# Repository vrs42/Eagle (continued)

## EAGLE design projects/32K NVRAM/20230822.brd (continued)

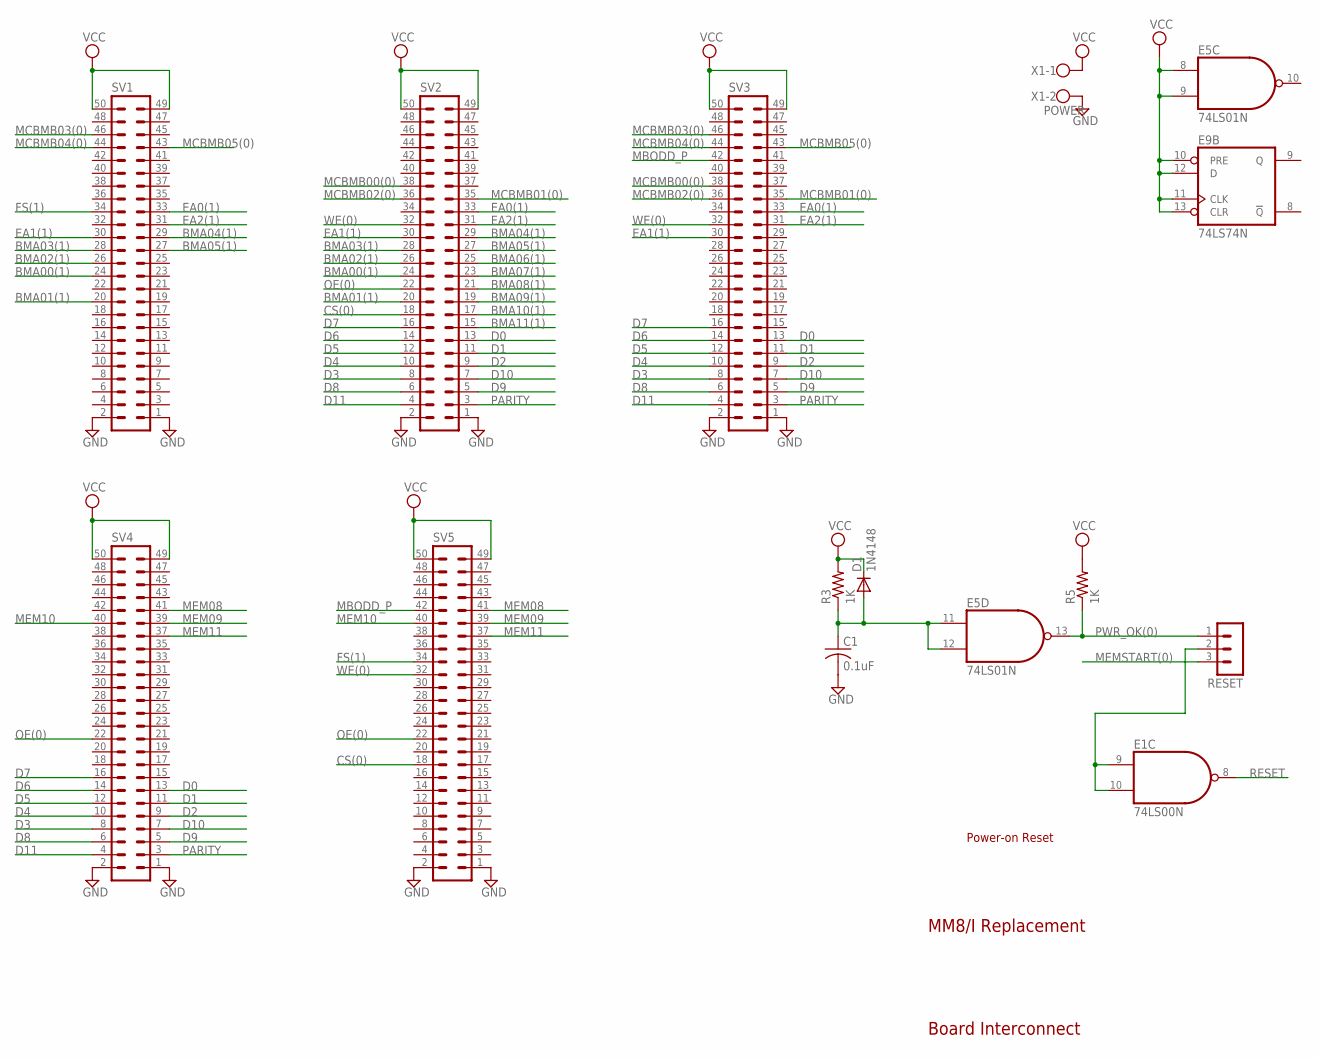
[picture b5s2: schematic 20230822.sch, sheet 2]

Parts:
C1: 0.1uF; C050-025X075
D1: 1N4148; DO35-10
E1: 74LS00N; DIL14
E5: 74LS01N; DIL14
E9: 74LS74N; DIL14
R3, R5: 1K; 0207/10
RESET: MA03-1
SV1, SV2, SV3, SV4, SV5: ML50L
X1: POWER; W237-102

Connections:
BMA00(1): SV1.24, SV2.24; also elsewhere on the board
BMA01(1): SV1.20, SV2.20; also elsewhere on the board
BMA02(1): SV1.26, SV2.26; also elsewhere on the board
BMA03(1): SV1.28, SV2.28; also elsewhere on the board
BMA04(1): SV1.29, SV2.29; also elsewhere on the board
BMA05(1): SV1.27, SV2.27; also elsewhere on the board
BMA06(1): SV2.25; also elsewhere on the board
BMA07(1): SV2.23; also elsewhere on the board
BMA08(1): SV2.21; also elsewhere on the board
BMA09(1): SV2.19; also elsewhere on the board
BMA10(1): SV2.17; also elsewhere on the board
BMA11(1): SV2.15; also elsewhere on the board
CS(0): SV2.18, SV5.18; also elsewhere on the board
D0: SV2.13, SV3.13, SV4.13; also elsewhere on the board
D1: SV2.11, SV3.11, SV4.11; also elsewhere on the board
D2: SV2.9, SV3.9, SV4.9; also elsewhere on the board
D3: SV2.8, SV3.8, SV4.8; also elsewhere on the board
D4: SV2.10, SV3.10, SV4.10; also elsewhere on the board
D5: SV2.12, SV3.12, SV4.12; also elsewhere on the board
D6: SV2.14, SV3.14, SV4.14; also elsewhere on the board
D7: SV2.16, SV3.16, SV4.16; also elsewhere on the board
D8: SV2.6, SV3.6, SV4.6; also elsewhere on the board
D9: SV2.5, SV3.5, SV4.5; also elsewhere on the board
D10: SV2.7, SV3.7, SV4.7; also elsewhere on the board
D11: SV2.4, SV3.4, SV4.4; also elsewhere on the board
EA0(1): SV1.33, SV2.33, SV3.33; also elsewhere on the board
EA1(1): SV1.30, SV2.30, SV3.30; also elsewhere on the board
EA2(1): SV1.31, SV2.31, SV3.31; also elsewhere on the board
FS(1): SV1.34, SV5.34; also elsewhere on the board
GND: C1.2, E1.7 (GND), E5.7 (GND), E9.7 (GND), SV1.1, SV1.2, SV2.1, SV2.2, SV3.1, SV3.2, SV4.1, SV4.2, SV5.1, SV5.2, X1.2; also elsewhere on the board
MBODD_P: SV3.42, SV5.42; also elsewhere on the board
MCBMB00(0): SV2.38, SV3.38; also elsewhere on the board
MCBMB01(0): SV2.35, SV3.35; also elsewhere on the board
MCBMB02(0): SV2.36, SV3.36; also elsewhere on the board
MCBMB03(0): SV1.46, SV3.46; also elsewhere on the board
MCBMB04(0): SV1.44, SV3.44; also elsewhere on the board
MCBMB05(0): SV1.43, SV3.43; also elsewhere on the board
MEM08: SV4.41, SV5.41; also elsewhere on the board
MEM09: SV4.39, SV5.39; also elsewhere on the board
MEM10: SV4.40, SV5.40; also elsewhere on the board
MEM11: SV4.37, SV5.37; also elsewhere on the board
MEMSTART(0): RESET.3; also elsewhere on the board
unnamed: E1.9 (I0), E1.10 (I1), RESET.2
OE(0): SV2.22, SV4.22, SV5.22; also elsewhere on the board
PARITY: SV2.3, SV3.3, SV4.3; also elsewhere on the board
PWR_OK: C1.1, D1.A, E5.11 (I0), E5.12 (I1), R3.1
PWR_OK(0): E5.13 (O), R5.1, RESET.1
RESET: E1.8 (O); also elsewhere on the board
VCC: D1.C, E1.14 (VCC), E5.8 (I0), E5.9 (I1), E5.14 (VCC), E9.10 (PRE), E9.11 (CLK), E9.12 (D), E9.13 (CLR), E9.14 (VCC), R3.2, R5.2, SV1.49, SV1.50, SV2.49, SV2.50, SV3.49, SV3.50, SV4.49, SV4.50, SV5.49, SV5.50, X1.1; also elsewhere on the board
WE(0): SV2.32, SV3.32, SV5.32; also elsewhere on the board

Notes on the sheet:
Board Interconnect
MM8/I Replacement
Power-on Reset

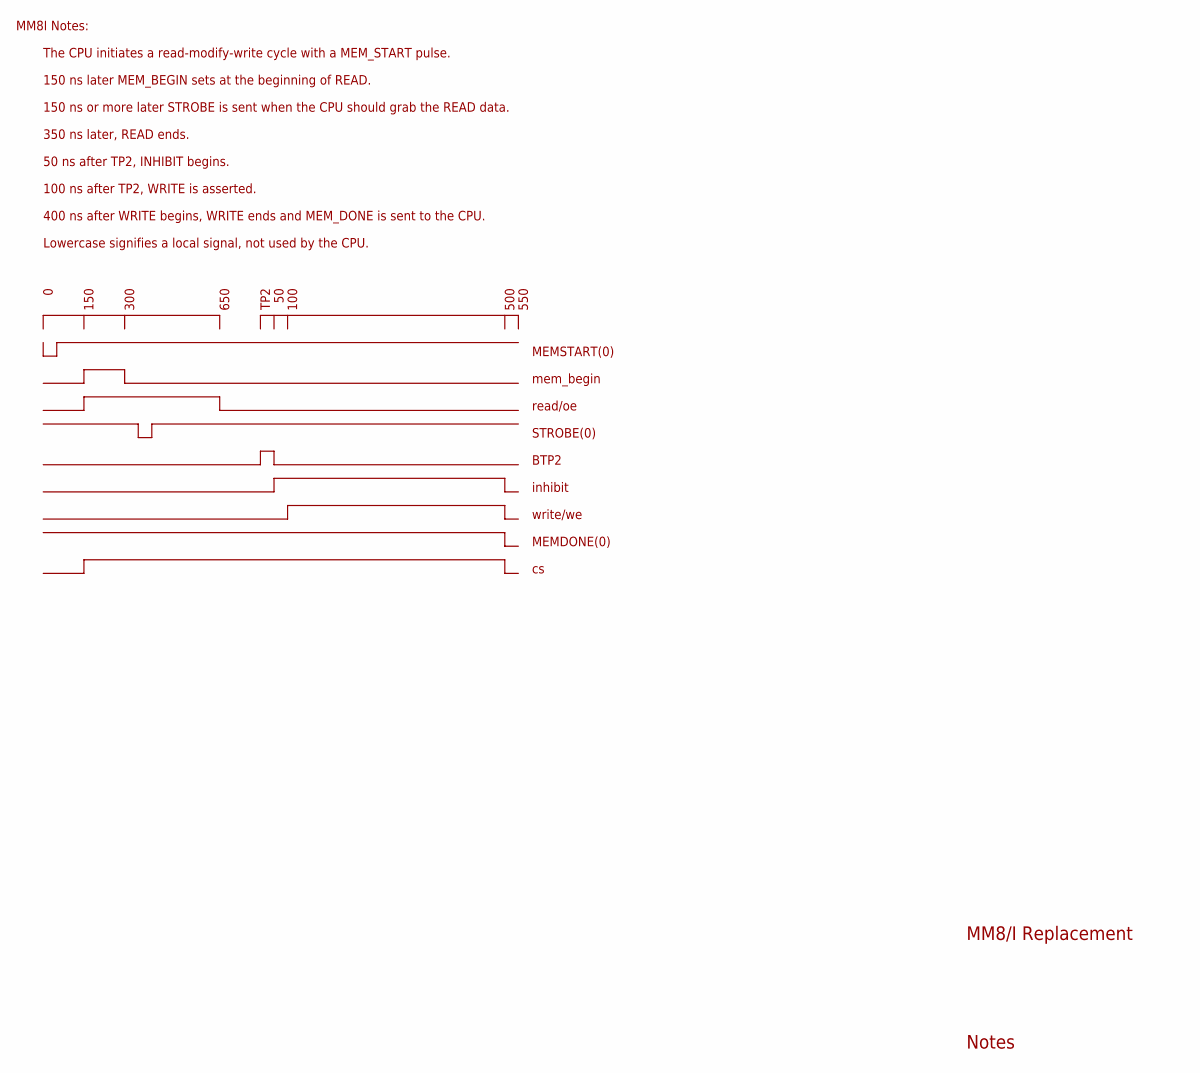
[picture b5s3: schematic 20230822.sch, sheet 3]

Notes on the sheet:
Notes
The CPU initiates a read-modify-write cycle with a MEM_START pulse.
150 ns later MEM_BEGIN sets at the beginning of READ.
150 ns or more later STROBE is sent when the CPU should grab the READ data.
50 ns after TP2, INHIBIT begins.
100 ns after TP2, WRITE is asserted.
400 ns after WRITE begins, WRITE ends and MEM_DONE is sent to the CPU.
350 ns later, READ ends.
150
300
650
TP2
100
500
MEMSTART(0)
mem_begin
read/oe
STROBE(0)
BTP2
inhibit
write/we
MEMDONE(0)
Lowercase signifies a local signal, not used by the CPU.
550
MM8I Notes:
MM8/I Replacement

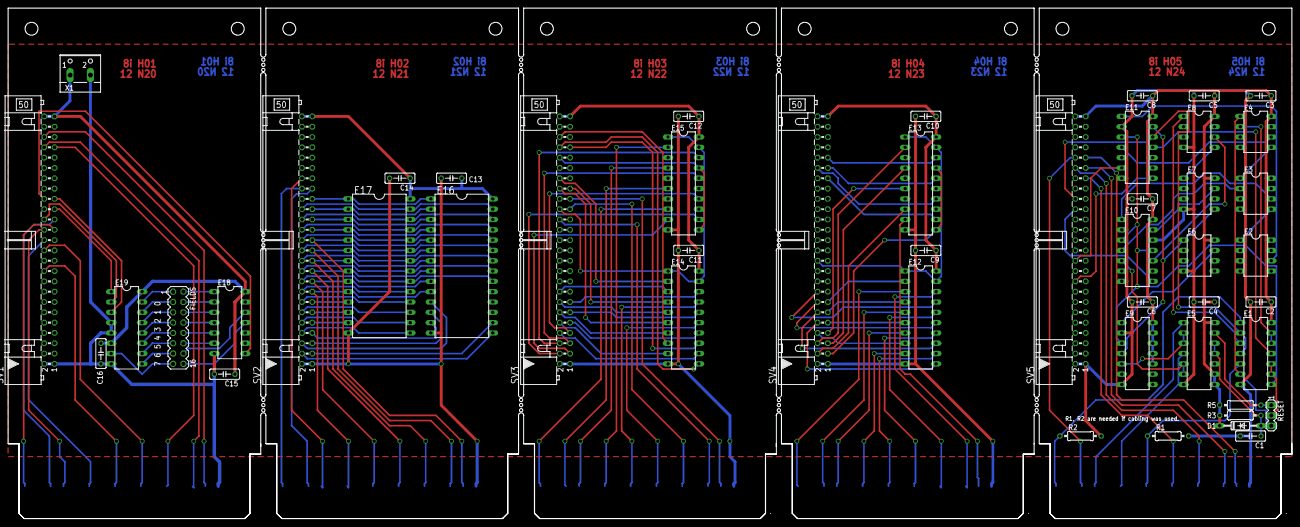
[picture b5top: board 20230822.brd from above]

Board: 2 copper layers, 316.2 x 125.7 mm, 54 parts (0 on the bottom side), 101 nets.

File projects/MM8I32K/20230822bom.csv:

Qty,Value,Device,Package,Parts,Description
5, ,EDGE-1,EDGE-CON1,"H01, H02, H03, H04, H05",Single-Sided DEC Edge Connector -- (side 2)
1, ,MA03-1,MA03-1,RESET,PIN HEADER
1, ,MA08-2,MA08-2,FIELDS,PIN HEADER
5, ,ML50L,ML50L,"SV1, SV2, SV3, SV4, SV5",HARTING
16,0.1uF,C-US050-025X075,C050-025X075,"C1, C2, C3, C4, C5, C6, C7, C8, C9, C10, C11, C12, C13, C14, C15, C16","CAPACITOR, American symbol"
2,100,R-US_0207/10,0207/10,"R1, R2","RESISTOR, American symbol"
2,1K,R-US_0207/10,0207/10,"R3, R5","RESISTOR, American symbol"
1,1N4148,1N4148DO35-10,DO35-10,D1,DIODE
1,74LS00N,74LS00N,DIL14,E1,Quad 2-input NAND gate
1,74LS01N,74LS01N,DIL14,E5,"Quad 2-input NAND gate, open collector"
1,74LS138N,74LS138N,DIL16,E19,3-line to 8-line DECODER/DEMULTIPLEXER
1,74LS30N,74LS30N,DIL14,E18,8-input NAND gate
3,74LS74N,74LS74N,DIL14,"E9, E10, E11","Dual D type positive edge triggered FLIP FLOP, preset and clear"
2,74S240N,74S240N,DIL20,"E14, E15","Octal BUFFER and LINE DRIVER, 3-state"
2,74S244N,74S244N,DIL20,"E12, E13","Octal BUFFER and LINE DRIVER, 3-state"
1,DECPROTO11111,DECPROTO11111,DECPROTO11111,U$6,Various small DEC boards stuck together with break-away tab routing.
2,DS1230,62256P,DIL28-6,"E16, E17",MEMORY
6,MXD1000,MXD1000,DIL08,"E2, E3, E4, E6, E7, E8",DELAY LINE
1,POWER,W237-102,W237-102,X1,WAGO SCREW CLAMP
